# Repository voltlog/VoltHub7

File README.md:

# VoltHub7
This respository will hold the HW design files for the VoltHub7 project.
More details on youtube in Voltlog #475.

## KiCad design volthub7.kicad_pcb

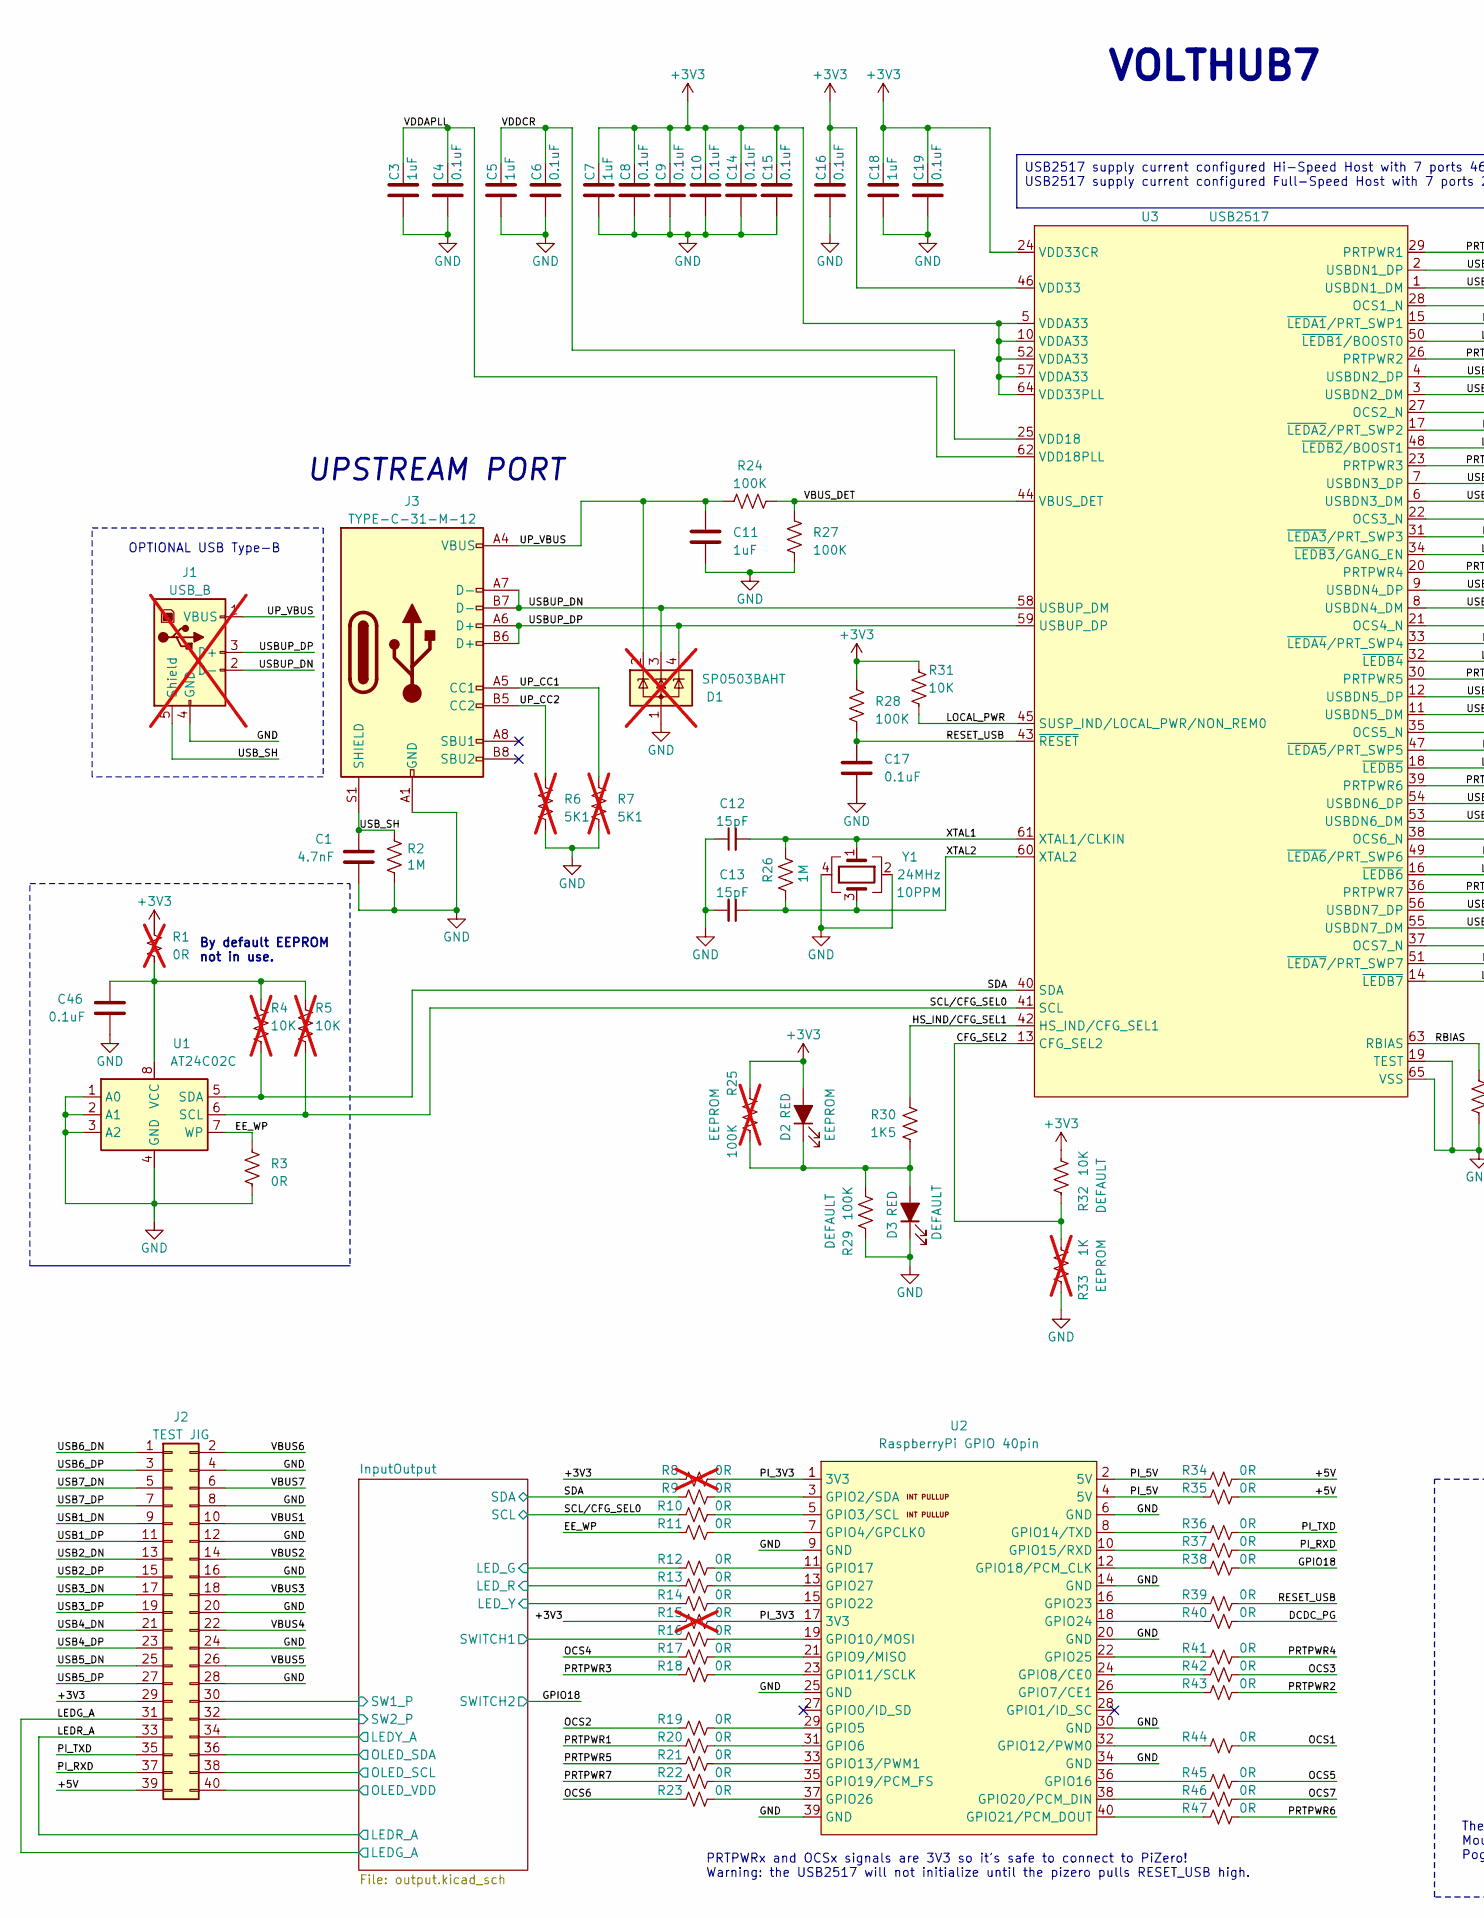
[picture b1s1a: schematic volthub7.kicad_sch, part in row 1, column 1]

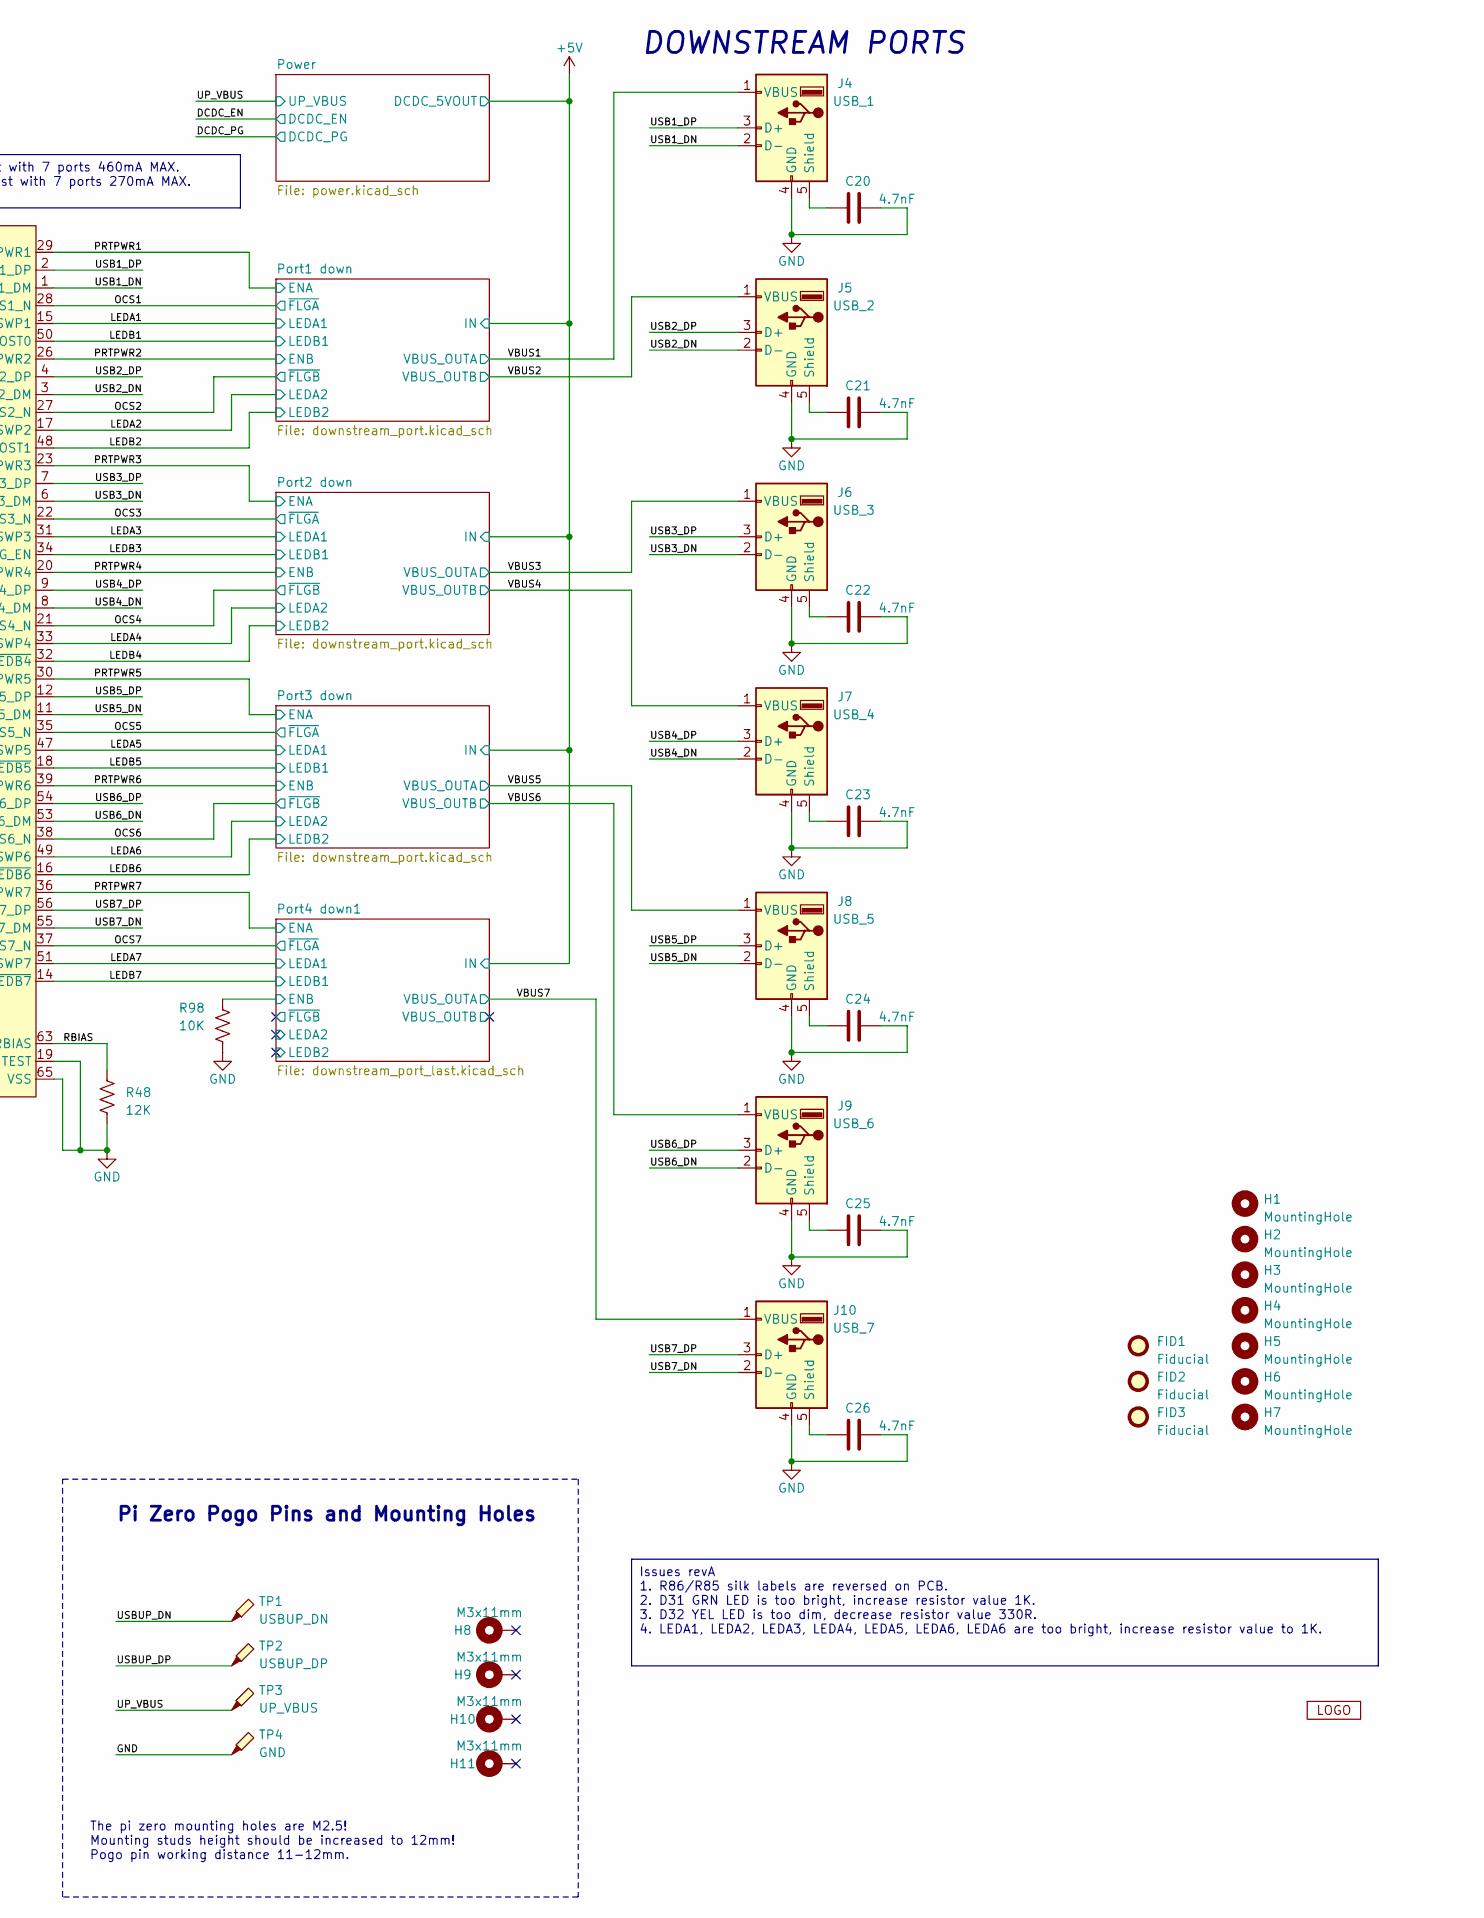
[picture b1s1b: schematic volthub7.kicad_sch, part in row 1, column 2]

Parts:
C1: 4.7nF; C_1206_3216Metric; LCSC C107198
C3, C5, C7, C11, C18: 1uF; C_0603_1608Metric
C4, C6, C8, C9, C10, C14, C15, C16, C17, C19, C46: 0.1uF; C_0603_1608Metric; LCSC C14663
C12, C13: 15pF; C_0603_1608Metric; LCSC C1644
C20, C21, C22, C23, C24, C25, C26: 4.7nF; C_1206_3216Metric; LCSC C24497
D1: SP0503BAHT; SOT-143; LCSC C2682275; not fitted
D2: EEPROM; LED_0603_1608Metric; LCSC C193902
D3: DEFAULT; LED_0603_1608Metric; LCSC C193902
FID1, FID2, FID3: Fiducial; Fiducial_0.5mm_Mask1mm
H1, H2, H3, H4, H5, H6, H7: MountingHole; MountingHole_3.2mm_M3
H8, H9, H10, H11: M3x11mm; SMTSO30100CTJ; LCSC C2916372
J1: USB_B; USB_B_Lumberg_2411_02_Horizontal; LCSC C530600; not fitted
J2: TEST JIG; JST_PHD_B32B-PHDSS_2x20_P2.00mm_Vertical; LCSC C2845630
J3: TYPE-C-31-M-12; USB_C_Receptacle_HRO_TYPE-C-31-M-12; LCSC C165948
J4: USB_1; USB_A_HRO_U-A-24DD-W-5; LCSC C530625
J5: USB_2; USB_A_HRO_U-A-24DD-W-5; LCSC C530625
J6: USB_3; USB_A_HRO_U-A-24DD-W-5; LCSC C530625
J7: USB_4; USB_A_HRO_U-A-24DD-W-5; LCSC C530625
J8: USB_5; USB_A_HRO_U-A-24DD-W-5; LCSC C530625
J9: USB_6; USB_A_HRO_U-A-24DD-W-5; LCSC C530625
J10: USB_7; USB_A_HRO_U-A-24DD-W-5; LCSC C530625
R1, R8, R15: 0R; R_0603_1608Metric; LCSC C21189; not fitted
R2: 1M; R_1206_3216Metric
R3, R9, R10, R11, R12, R13, R14, R16, R17, R18, R19, R20, R21, R22, R23, R34, R35, R36, R37, R38, R39, R40, R41, R42, R43, R44, R45, R46, R47: 0R; R_0603_1608Metric; LCSC C21189
R4, R5: 10K; R_0603_1608Metric; LCSC C25804; not fitted
R6, R7: 5K1; R_0603_1608Metric; not fitted
R24, R27, R28, R29: 100K; R_0603_1608Metric; LCSC C25803
R25: 100K; R_0603_1608Metric; LCSC C25803; not fitted
R26: 1M; R_0603_1608Metric; LCSC C22935
R30: 1K5; R_0603_1608Metric; LCSC C21190
R31, R32, R98: 10K; R_0603_1608Metric; LCSC C25804
R33: 1K; R_0603_1608Metric; LCSC C21190; not fitted
R48: 12K; R_0603_1608Metric; LCSC C22790
TP1: USBUP_DN; Pogo_pin_YZ87615160P-01; LCSC C5157295
TP2: USBUP_DP; Pogo_pin_YZ87615160P-01; LCSC C5157295
TP3: UP_VBUS; Pogo_pin_YZ87615160P-01; LCSC C5157295
TP4: GND; Pogo_pin_YZ87615160P-01; LCSC C5157295
U1: AT24C02C; SOIC-8_3.9x4.9mm_P1.27mm; LCSC C6203
U2: RaspberryPi GPIO 40pin; RaspberryPi_Zero2W_40Pin
U3: USB2517; QFN-64-1EP_9x9mm_P0.5mm_EP4.7x4.7mm; LCSC C1521556
V1: VOLTLOG_LOGO; voltlog_mask_5mm
Y1: 24MHz; Crystal_SMD_SeikoEpson_TSX3225-4Pin_3.2x2.5mm; Tolerance 10PPM; LCSC C89577

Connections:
+3V3: C7.1, C8.1, C9.1, C10.1, C14.1, C15.1, C16.1, C18.1, C19.1, D2.2 (A), J2.29, R1.2, R8.1, R15.1, R25.1, R28.2, R31.2, R32.2, U3.5 (VDDA33), U3.10 (VDDA33), U3.24 (VDD33CR), U3.46 (VDD33), U3.52 (VDDA33), U3.57 (VDDA33), U3.64 (VDD33PLL); also elsewhere on the board
+5V: J2.39, R34.2, R35.2; also elsewhere on the board
/CFG_SEL2: R32.1, R33.2, U3.13 (CFG_SEL2)
/DCDC_PG: R40.2; also elsewhere on the board
/EE_WP: R3.2, R11.1, U1.7 (WP)
/GPIO18: R38.2; also elsewhere on the board
/HS_IND/CFG_SEL1: R30.2, U3.42 (HS_IND/CFG_SEL1)
/LEDA1: U3.15 (~LEDA1/PRT_SWP1); also elsewhere on the board
/LEDA2: U3.17 (~LEDA2/PRT_SWP2); also elsewhere on the board
/LEDA3: U3.31 (~LEDA3/PRT_SWP3); also elsewhere on the board
/LEDA4: U3.33 (~LEDA4/PRT_SWP4); also elsewhere on the board
/LEDA5: U3.47 (~LEDA5/PRT_SWP5); also elsewhere on the board
/LEDA6: U3.49 (~LEDA6/PRT_SWP6); also elsewhere on the board
/LEDA7: U3.51 (~LEDA7/PRT_SWP7); also elsewhere on the board
/LEDB1: U3.50 (~LEDB1/BOOST0); also elsewhere on the board
/LEDB2: U3.48 (~LEDB2/BOOST1); also elsewhere on the board
/LEDB3: U3.34 (~LEDB3/GANG_EN); also elsewhere on the board
/LEDB4: U3.32 (~LEDB4); also elsewhere on the board
/LEDB5: U3.18 (~LEDB5); also elsewhere on the board
/LEDB6: U3.16 (~LEDB6); also elsewhere on the board
/LEDB7: U3.14 (~LEDB7); also elsewhere on the board
/LEDG_A: J2.31; also elsewhere on the board
/LEDR_A: J2.33; also elsewhere on the board
/LOCAL_PWR: R31.1, U3.45 (SUSP_IND/LOCAL_PWR/NON_REM0)
/OCS1: R44.2, U3.28 (OCS1_N); also elsewhere on the board
/OCS2: R19.1, U3.27 (OCS2_N); also elsewhere on the board
/OCS3: R42.2, U3.22 (OCS3_N); also elsewhere on the board
/OCS4: R17.1, U3.21 (OCS4_N); also elsewhere on the board
/OCS5: R45.2, U3.35 (OCS5_N); also elsewhere on the board
/OCS6: R23.1, U3.38 (OCS6_N); also elsewhere on the board
/OCS7: R46.2, U3.37 (OCS7_N); also elsewhere on the board
/Output/LEDY_A: J2.34; also elsewhere on the board
/Output/LED_G: R12.1; also elsewhere on the board
/Output/LED_R: R13.1; also elsewhere on the board
/Output/LED_Y: R14.1; also elsewhere on the board
/Output/OLED_SCL: J2.38; also elsewhere on the board
/Output/OLED_SDA: J2.36; also elsewhere on the board
/Output/OLED_VDD: J2.40; also elsewhere on the board
/Output/SW1_P: J2.30; also elsewhere on the board
/Output/SW2_P: J2.32; also elsewhere on the board
/Output/SWITCH1: R16.1; also elsewhere on the board
/PI_3V3: R8.2, R15.2, U2.1 (3V3), U2.17 (3V3)
/PI_5V: R34.1, R35.1, U2.2 (5V), U2.4 (5V)
/PI_RXD: J2.37, R37.2
/PI_TXD: J2.35, R36.2
/PRTPWR1: R20.1, U3.29 (PRTPWR1); also elsewhere on the board
/PRTPWR2: R43.2, U3.26 (PRTPWR2); also elsewhere on the board
/PRTPWR3: R18.1, U3.23 (PRTPWR3); also elsewhere on the board
/PRTPWR4: R41.2, U3.20 (PRTPWR4); also elsewhere on the board
/PRTPWR5: R21.1, U3.30 (PRTPWR5); also elsewhere on the board
/PRTPWR6: R47.2, U3.39 (PRTPWR6); also elsewhere on the board
/PRTPWR7: R22.1, U3.36 (PRTPWR7); also elsewhere on the board
/Port4 down1/ENB: R98.2; also elsewhere on the board
/RBIAS: R48.2, U3.63 (RBIAS)
/RESET_USB: C17.1, R28.1, R39.2, U3.43 (~RESET)
/SCL/CFG_SEL0: R5.1, R10.1, U1.6 (SCL), U3.41 (SCL); also elsewhere on the board
/SDA: R4.1, R9.1, U1.5 (SDA), U3.40 (SDA); also elsewhere on the board
/UP_CC1: J3.A5 (CC1), R7.2
/UP_CC2: J3.B5 (CC2), R6.2
/UP_VBUS: C11.1, D1.2 (K), J1.1 (VBUS), J3.A4 (VBUS), J3.A9 (VBUS), J3.B4 (VBUS), J3.B9 (VBUS), R24.1, TP3.1; also elsewhere on the board
/USB1_DN: J2.9, J4.2 (D-), U3.1 (USBDN1_DM)
/USB1_DP: J2.11, J4.3 (D+), U3.2 (USBDN1_DP)
/USB2_DN: J2.13, J5.2 (D-), U3.3 (USBDN2_DM)
/USB2_DP: J2.15, J5.3 (D+), U3.4 (USBDN2_DP)
/USB3_DN: J2.17, J6.2 (D-), U3.6 (USBDN3_DM)
/USB3_DP: J2.19, J6.3 (D+), U3.7 (USBDN3_DP)
/USB4_DN: J2.21, J7.2 (D-), U3.8 (USBDN4_DM)
/USB4_DP: J2.23, J7.3 (D+), U3.9 (USBDN4_DP)
/USB5_DN: J2.25, J8.2 (D-), U3.11 (USBDN5_DM)
/USB5_DP: J2.27, J8.3 (D+), U3.12 (USBDN5_DP)
/USB6_DN: J2.1, J9.2 (D-), U3.53 (USBDN6_DM)
/USB6_DP: J2.3, J9.3 (D+), U3.54 (USBDN6_DP)
/USB7_DN: J2.5, J10.2 (D-), U3.55 (USBDN7_DM)
/USB7_DP: J2.7, J10.3 (D+), U3.56 (USBDN7_DP)
/USBUP_DN: D1.3 (K), J1.2 (D-), J3.A7 (D-), J3.B7 (D-), TP1.1, U3.58 (USBUP_DM)
/USBUP_DP: D1.4 (K), J1.3 (D+), J3.A6 (D+), J3.B6 (D+), TP2.1, U3.59 (USBUP_DP)
/VBUS1: J2.10, J4.1 (VBUS); also elsewhere on the board
/VBUS2: J2.14, J5.1 (VBUS); also elsewhere on the board
/VBUS3: J2.18, J6.1 (VBUS); also elsewhere on the board
/VBUS4: J2.22, J7.1 (VBUS); also elsewhere on the board
/VBUS5: J2.26, J8.1 (VBUS); also elsewhere on the board
/VBUS6: J2.2, J9.1 (VBUS); also elsewhere on the board
/VBUS7: J2.6, J10.1 (VBUS); also elsewhere on the board
/VBUS_DET: R24.2, R27.2, U3.44 (VBUS_DET)
/VDDAPLL: C3.1, C4.1, U3.62 (VDD18PLL)
/VDDCR: C5.1, C6.1, U3.25 (VDD18)
/XTAL1: C12.2, R26.2, U3.61 (XTAL1/CLKIN), Y1.1
/XTAL2: C13.1, R26.1, U3.60 (XTAL2), Y1.3
GND: C1.2, C3.2, C4.2, C5.2, C6.2, C7.2, C8.2, C9.2, C10.2, C11.2, C12.1, C13.2, C14.2, C15.2, C16.2, C17.2, C18.2, C19.2, C20.2, C21.2, C22.2, C23.2, C24.2, C25.2, C26.2, D1.1 (A), D3.1 (K), J1.4 (GND), J2.4, J2.8, J2.12, J2.16, J2.20, J2.24, J2.28, J3.A1 (GND), J3.A12 (GND), J3.B1 (GND), J3.B12 (GND), J4.4 (GND), J5.4 (GND), J6.4 (GND), J7.4 (GND), J8.4 (GND), J9.4 (GND), J10.4 (GND), R2.2, R3.1, R6.1, R7.1, R27.1, R29.2, R33.1, R48.1, R98.1, TP4.1, U1.1 (A0), U1.2 (A1), U1.3 (A2), U1.4 (GND), U2.6 (GND), U2.9 (GND), U2.14 (GND), U2.20 (GND), U2.25 (GND), U2.30 (GND), U2.34 (GND), U2.39 (GND), U3.19 (TEST), U3.65 (VSS), Y1.2, Y1.4; also elsewhere on the board
unnamed: D2.1 (K), D3.2 (A), R25.2, R29.1, R30.1
unnamed: C20.1, J4.5 (Shield)
unnamed: C21.1, J5.5 (Shield)
unnamed: C22.1, J6.5 (Shield)
unnamed: C23.1, J7.5 (Shield)
unnamed: C24.1, J8.5 (Shield)
unnamed: C25.1, J9.5 (Shield)
unnamed: C26.1, J10.5 (Shield)
unnamed: R9.2, U2.3 (GPIO2/SDA)
unnamed: R10.2, U2.5 (GPIO3/SCL)
unnamed: R11.2, U2.7 (GPIO4/GPCLK0)
unnamed: R19.2, U2.29 (GPIO5)
unnamed: R20.2, U2.31 (GPIO6)
unnamed: R43.1, U2.26 (GPIO7/CE1)
unnamed: R42.1, U2.24 (GPIO8/CE0)
unnamed: R17.2, U2.21 (GPIO9/MISO)
unnamed: R16.2, U2.19 (GPIO10/MOSI)
unnamed: R18.2, U2.23 (GPIO11/SCLK)
unnamed: R44.1, U2.32 (GPIO12/PWM0)
unnamed: R21.2, U2.33 (GPIO13/PWM1)
unnamed: R36.1, U2.8 (GPIO14/TXD)
unnamed: R37.1, U2.10 (GPIO15/RXD)
unnamed: R45.1, U2.36 (GPIO16)
unnamed: R12.2, U2.11 (GPIO17)
unnamed: R38.1, U2.12 (GPIO18/PCM_CLK)
unnamed: R22.2, U2.35 (GPIO19/PCM_FS)
unnamed: R46.1, U2.38 (GPIO20/PCM_DIN)
unnamed: R47.1, U2.40 (GPIO21/PCM_DOUT)
unnamed: R14.2, U2.15 (GPIO22)
unnamed: R39.1, U2.16 (GPIO23)
unnamed: R40.1, U2.18 (GPIO24)
unnamed: R41.1, U2.22 (GPIO25)
unnamed: R23.2, U2.37 (GPIO26)
unnamed: R13.2, U2.13 (GPIO27)

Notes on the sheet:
USB2517 supply current configured Hi-Speed Host with 7 ports 460mA MAX. USB2517 supply current configured Full-Speed Host with 7 ports 270mA MAX.
Issues revA 1. R86/R85 silk labels are reversed on PCB. 2. D31 GRN LED is too bright, increase resistor value 1K. 3. D32 YEL LED is too dim, decrease resistor value 330R. 4. LEDA1, LEDA2, LEDA3, LEDA4, LEDA5, LEDA6, LEDA6 are too bright, increase resistor value to 1K.
The pi zero mounting holes are M2.5! Mounting studs height should be increased to 12mm! Pogo pin working distance 11-12mm.
PRTPWRx and OCSx signals are 3V3 so it's safe to connect to PiZero! Warning: the USB2517 will not initialize until the pizero pulls RESET_USB high.
OPTIONAL USB Type-B
UPSTREAM PORT
VOLTHUB7
By default EEPROM not in use.
Pi Zero Pogo Pins and Mounting Holes
DOWNSTREAM PORTS

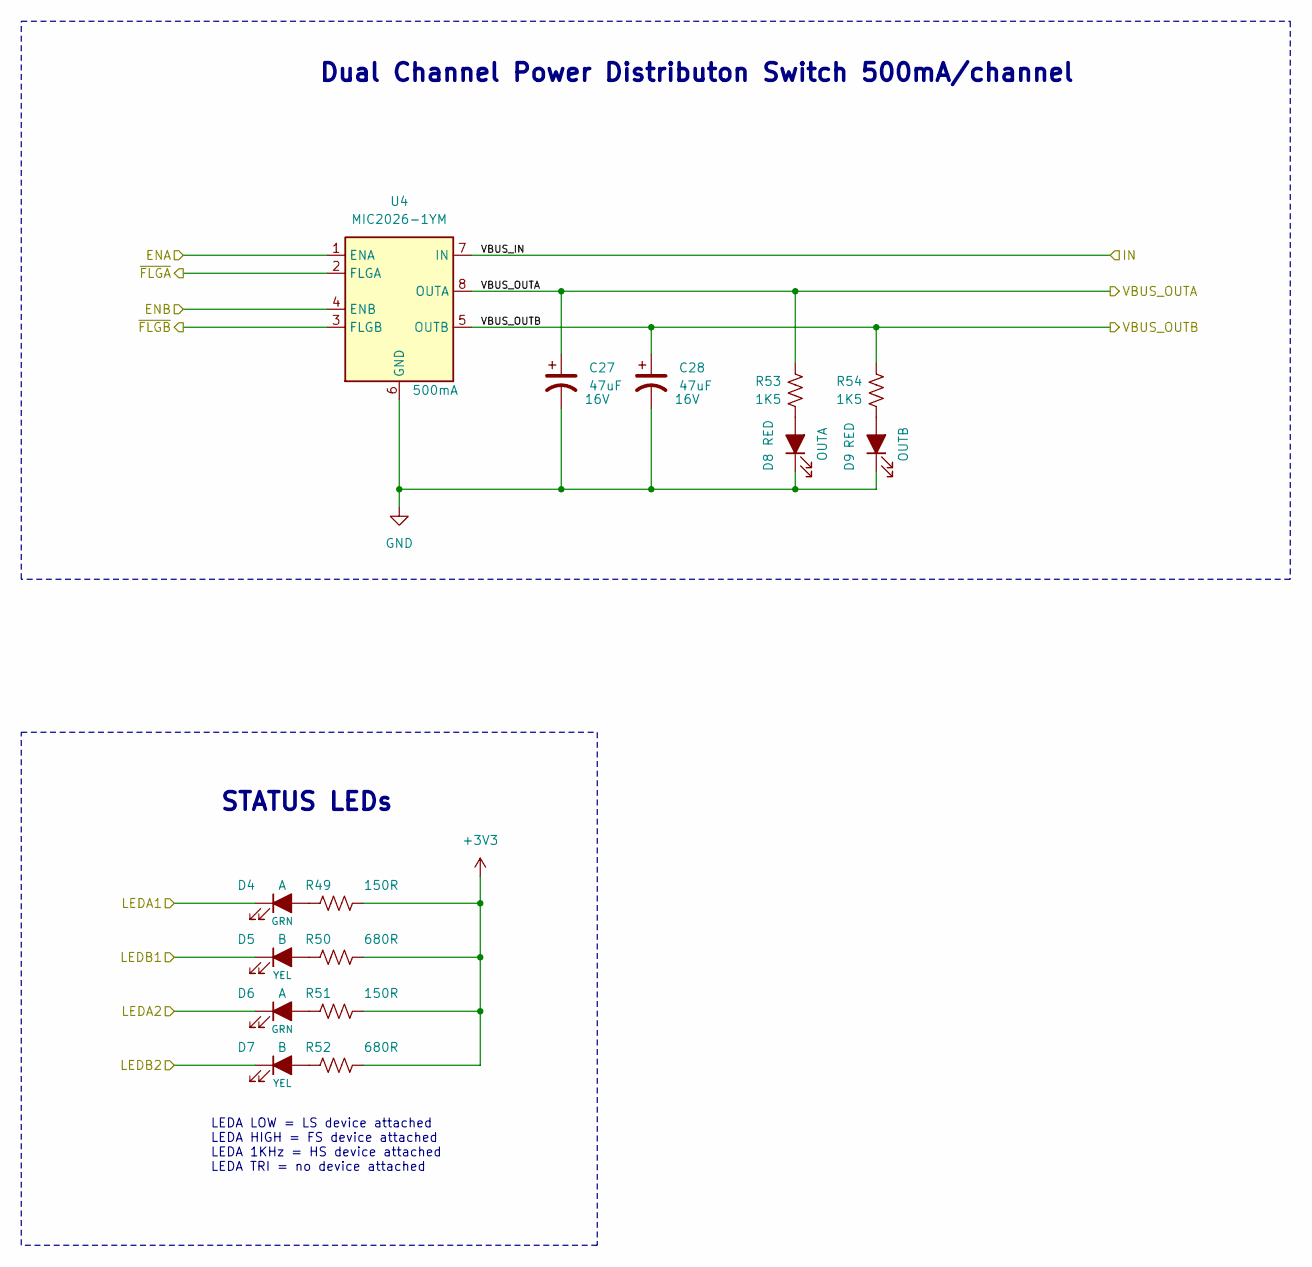
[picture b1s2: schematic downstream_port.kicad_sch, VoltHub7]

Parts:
C27, C28: 47uF; CP_Elec_6.3x5.3; Voltage 16V; LCSC C249535
D4, D6: A; LED_0603_1608Metric; LCSC C84267
D5, D7: B; LED_0603_1608Metric; LCSC C84268
D8: OUTA; LED_0603_1608Metric; LCSC C193902
D9: OUTB; LED_0603_1608Metric; LCSC C193902
R49, R51: 150R; R_0603_1608Metric; LCSC C22808
R50, R52: 680R; R_0603_1608Metric; LCSC C23228
R53, R54: 1K5; R_0603_1608Metric
U4: MIC2026-1YM; SO-8_3.9x4.9mm_P1.27mm; LCSC C144190

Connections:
+3V3: R49.2, R50.2, R51.2, R52.2; also elsewhere on the board
+5V: U4.7 (IN); also elsewhere on the board
/LEDA1: D4.1 (K); also elsewhere on the board
/LEDA2: D6.1 (K); also elsewhere on the board
/LEDB1: D5.1 (K); also elsewhere on the board
/LEDB2: D7.1 (K); also elsewhere on the board
/OCS1: U4.2 (FLGA); also elsewhere on the board
/OCS2: U4.3 (FLGB); also elsewhere on the board
/PRTPWR1: U4.1 (ENA); also elsewhere on the board
/PRTPWR2: U4.4 (ENB); also elsewhere on the board
/VBUS1: C27.1, R53.2, U4.8 (OUTA); also elsewhere on the board
/VBUS2: C28.1, R54.2, U4.5 (OUTB); also elsewhere on the board
GND: C27.2, C28.2, D8.1 (K), D9.1 (K), U4.6 (GND); also elsewhere on the board
unnamed: D4.2 (A), R49.1
unnamed: D5.2 (A), R50.1
unnamed: D6.2 (A), R51.1
unnamed: D7.2 (A), R52.1
unnamed: D8.2 (A), R53.1
unnamed: D9.2 (A), R54.1

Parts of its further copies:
C38, C39, C40, C41: 47uF; CP_Elec_6.3x5.3; Voltage 16V; LCSC C249535
D12, D14, D18, D20: A; LED_0603_1608Metric; LCSC C84267
D13, D15, D19, D21: B; LED_0603_1608Metric; LCSC C84268
D16, D22: OUTA; LED_0603_1608Metric; LCSC C193902
D17, D23: OUTB; LED_0603_1608Metric; LCSC C193902
R64, R66, R70, R72: 150R; R_0603_1608Metric; LCSC C22808
R65, R67, R71, R73: 680R; R_0603_1608Metric; LCSC C23228
R68, R69, R74, R75: 1K5; R_0603_1608Metric
U7, U8: MIC2026-1YM; SO-8_3.9x4.9mm_P1.27mm; LCSC C144190

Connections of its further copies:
+3V3: R64.2, R65.2, R66.2, R67.2, R70.2, R71.2, R72.2, R73.2; also elsewhere on the board
+5V: U7.7 (IN), U8.7 (IN); also elsewhere on the board
/LEDA3: D12.1 (K); also elsewhere on the board
/LEDA4: D14.1 (K); also elsewhere on the board
/LEDA5: D18.1 (K); also elsewhere on the board
/LEDA6: D20.1 (K); also elsewhere on the board
/LEDB3: D13.1 (K); also elsewhere on the board
/LEDB4: D15.1 (K); also elsewhere on the board
/LEDB5: D19.1 (K); also elsewhere on the board
/LEDB6: D21.1 (K); also elsewhere on the board
/OCS3: U7.2 (FLGA); also elsewhere on the board
/OCS4: U7.3 (FLGB); also elsewhere on the board
/OCS5: U8.2 (FLGA); also elsewhere on the board
/OCS6: U8.3 (FLGB); also elsewhere on the board
/PRTPWR3: U7.1 (ENA); also elsewhere on the board
/PRTPWR4: U7.4 (ENB); also elsewhere on the board
/PRTPWR5: U8.1 (ENA); also elsewhere on the board
/PRTPWR6: U8.4 (ENB); also elsewhere on the board
/VBUS3: C38.1, R68.2, U7.8 (OUTA); also elsewhere on the board
/VBUS4: C39.1, R69.2, U7.5 (OUTB); also elsewhere on the board
/VBUS5: C40.1, R74.2, U8.8 (OUTA); also elsewhere on the board
/VBUS6: C41.1, R75.2, U8.5 (OUTB); also elsewhere on the board
GND: C38.2, C39.2, C40.2, C41.2, D16.1 (K), D17.1 (K), D22.1 (K), D23.1 (K), U7.6 (GND), U8.6 (GND); also elsewhere on the board
unnamed: D12.2 (A), R64.1
unnamed: D13.2 (A), R65.1
unnamed: D14.2 (A), R66.1
unnamed: D15.2 (A), R67.1
unnamed: D16.2 (A), R68.1
unnamed: D17.2 (A), R69.1
unnamed: D18.2 (A), R70.1
unnamed: D19.2 (A), R71.1
unnamed: D20.2 (A), R72.1
unnamed: D21.2 (A), R73.1
unnamed: D22.2 (A), R74.1
unnamed: D23.2 (A), R75.1

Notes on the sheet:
Dual Channel Power Distributon Switch 500mA/channel
STATUS LEDs
LEDA LOW = LS device attached LEDA HIGH = FS device attached LEDA 1KHz = HS device attached LEDA TRI = no device attached

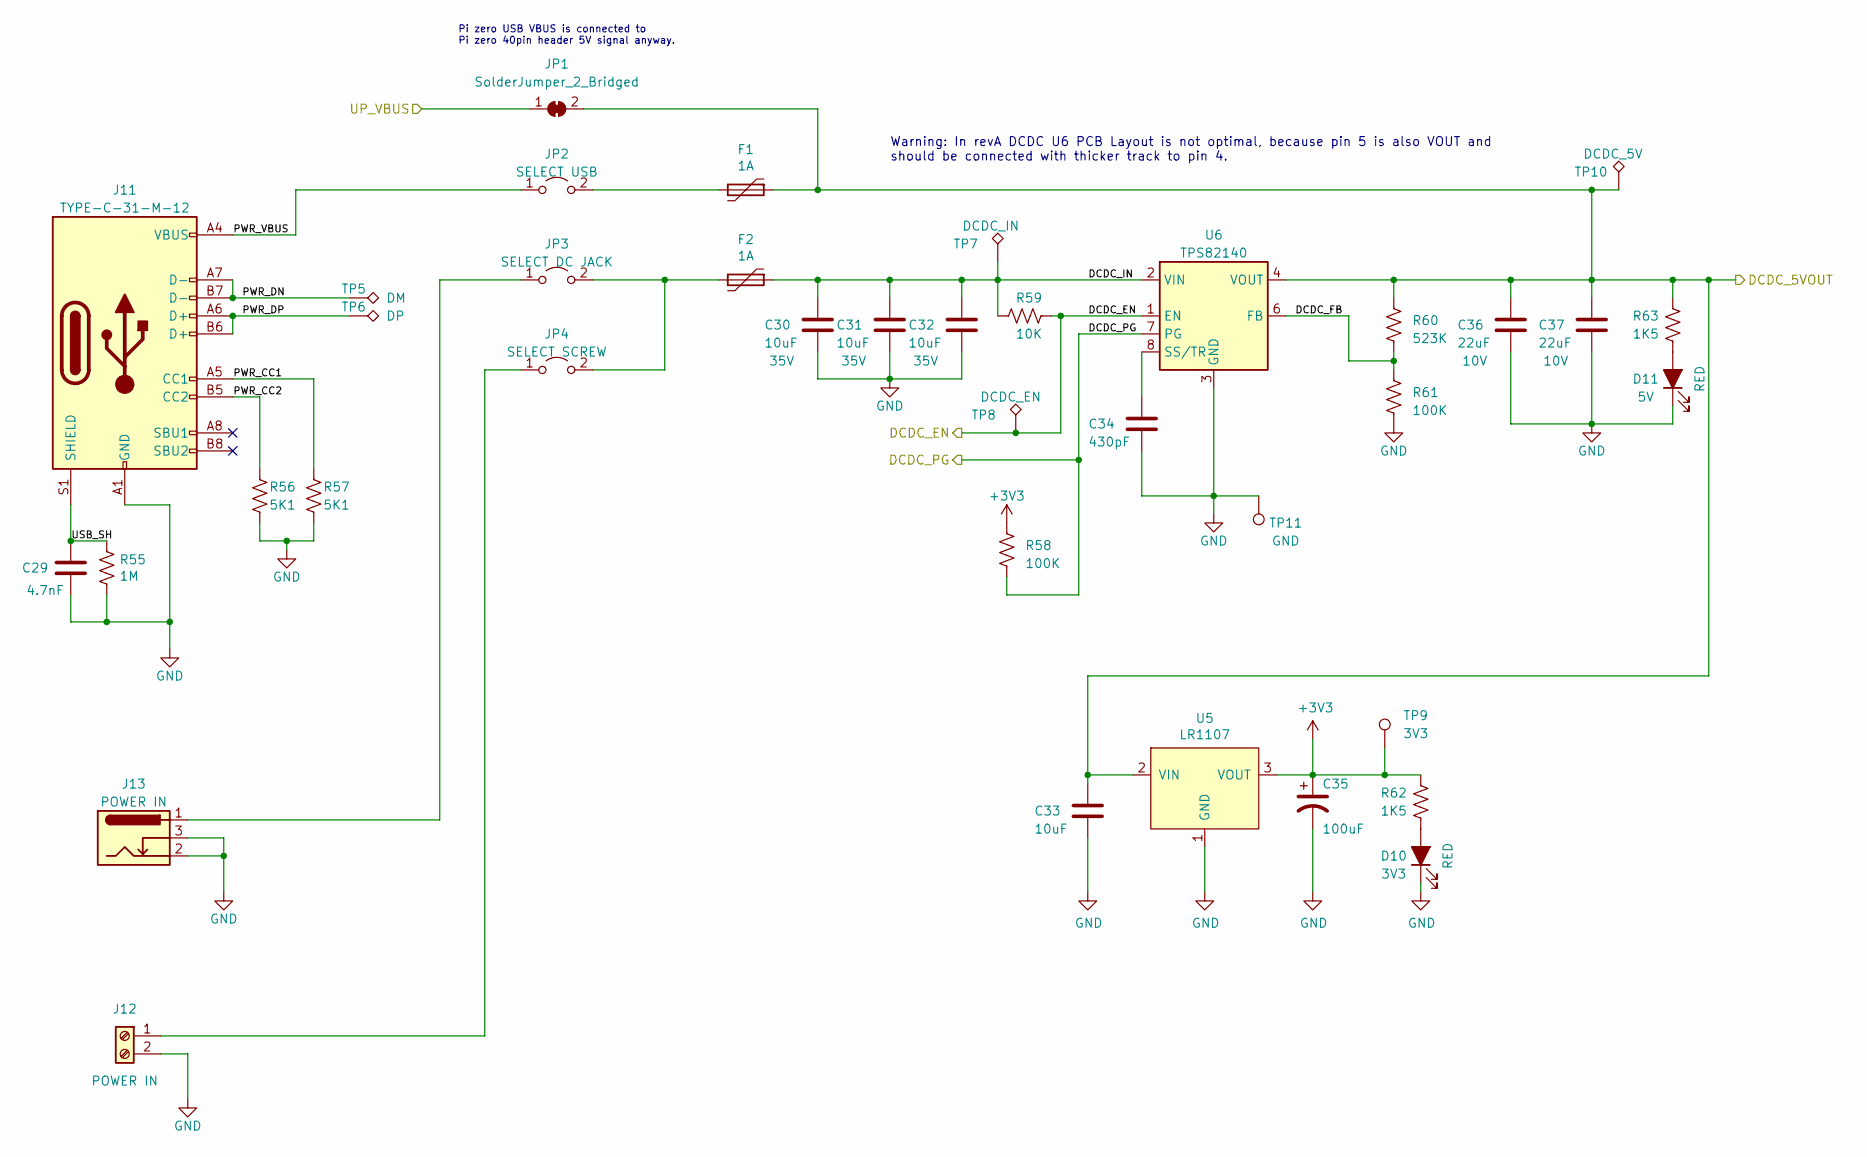
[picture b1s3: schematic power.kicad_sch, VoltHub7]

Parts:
C29: 4.7nF; C_1206_3216Metric; LCSC C107198
C30, C31, C32, C33: 10uF; C_0805_2012Metric; Voltage 35V; LCSC C162422
C34: 430pF; C_0603_1608Metric; LCSC C309472
C35: 100uF; CP_Elec_6.3x5.8; Voltage 10V; LCSC C340720
C36, C37: 22uF; C_0805_2012Metric; Voltage 10V; LCSC C29277
D10: 3V3; LED_0603_1608Metric; LCSC C193902
D11: 5V; LED_0603_1608Metric; LCSC C193902
F1, F2: 1A; Fuse_0805_2012Metric; LCSC C369152
J11: TYPE-C-31-M-12; USB_C_Receptacle_HRO_TYPE-C-31-M-12; LCSC C165948
J12: POWER IN; TerminalBlock_RND_205-00287_1x02_P5.08mm_Horizontal
J13: POWER IN; BarrelJack_CLIFF_FC681465S_SMT_Horizontal; LCSC C2987414
JP1: SolderJumper_2_Bridged; SolderJumper-2_P1.3mm_Bridged_RoundedPad1.0x1.5mm
JP2: SELECT USB; PinHeader_1x02_P2.54mm_Vertical
JP3: SELECT DC JACK; PinHeader_1x02_P2.54mm_Vertical
JP4: SELECT SCREW; PinHeader_1x02_P2.54mm_Vertical
R55: 1M; R_1206_3216Metric
R56, R57: 5K1; R_0603_1608Metric
R58, R61: 100K; R_0603_1608Metric; LCSC C25803
R59: 10K; R_0603_1608Metric; LCSC C25804
R60: 523K; R_0603_1608Metric; LCSC C5126197
R62: 1K5; R_0603_1608Metric; LCSC C21190
R63: 1K5; R_0603_1608Metric
TP5: DM; TestPoint_Pad_D1.0mm
TP6: DP; TestPoint_Pad_D1.0mm
TP7: DCDC_IN; TestPoint_Pad_D1.0mm
TP8: DCDC_EN; TestPoint_Pad_D1.0mm
TP9: 3V3; TestPoint_Pad_D1.0mm
TP10: DCDC_5V; TestPoint_Pad_D1.0mm
TP11: GND; TestPoint_Keystone_5019_Minature; LCSC C238131
U5: LR1107; SOT-89-3; LCSC C171498
U6: TPS82140; Texas_SIL0008D_MicroSiP-8-1EP_2.8x3mm_P0.65mm_EP1.1x1.9mm

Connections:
+3V3: C35.1, R58.2, R62.2, TP9.1, U5.3 (VOUT); also elsewhere on the board
+5V: C33.1, C36.1, C37.1, F1.1, JP1.2 (B), R60.2, R63.2, TP10.1, U5.2 (VIN), U6.4 (VOUT), U6.5 (VOUT); also elsewhere on the board
/DCDC_EN: R59.1, TP8.1, U6.1 (EN)
/DCDC_PG: R58.1, U6.7 (PG); also elsewhere on the board
/Power/DCDC_FB: R60.1, R61.2, U6.6 (FB)
/Power/DCDC_IN: C30.1, C31.1, C32.1, F2.1, R59.2, TP7.1, U6.2 (VIN)
/Power/PWR_CC1: J11.A5 (CC1), R57.2
/Power/PWR_CC2: J11.B5 (CC2), R56.2
/Power/PWR_DN: J11.A7 (D-), J11.B7 (D-), TP5.1
/Power/PWR_DP: J11.A6 (D+), J11.B6 (D+), TP6.1
/Power/PWR_VBUS: J11.A4 (VBUS), J11.A9 (VBUS), J11.B4 (VBUS), J11.B9 (VBUS), JP2.1 (A)
/Power/USB_SH: C29.1, J11.S1 (SHIELD), R55.1
/UP_VBUS: JP1.1 (A); also elsewhere on the board
GND: C29.2, C30.2, C31.2, C32.2, C33.2, C34.2, C35.2, C36.2, C37.2, D10.1 (K), D11.1 (K), J11.A1 (GND), J11.A12 (GND), J11.B1 (GND), J11.B12 (GND), J12.2, J13.2, J13.3, R55.2, R56.1, R57.1, R61.1, TP11.1, U5.1 (GND), U6.3 (GND), U6.9 (GND); also elsewhere on the board
unnamed: D10.2 (A), R62.1
unnamed: D11.2 (A), R63.1
unnamed: J12.1, JP4.1 (A)
unnamed: F1.2, JP2.2 (B)
unnamed: J13.1, JP3.1 (A)
unnamed: F2.2, JP3.2 (B), JP4.2 (B)
unnamed: C34.1, U6.8 (SS/TR)

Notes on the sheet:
Pi zero USB VBUS is connected to Pi zero 40pin header 5V signal anyway.
Warning: In revA DCDC U6 PCB Layout is not optimal, because pin 5 is also VOUT and should be connected with thicker track to pin 4.

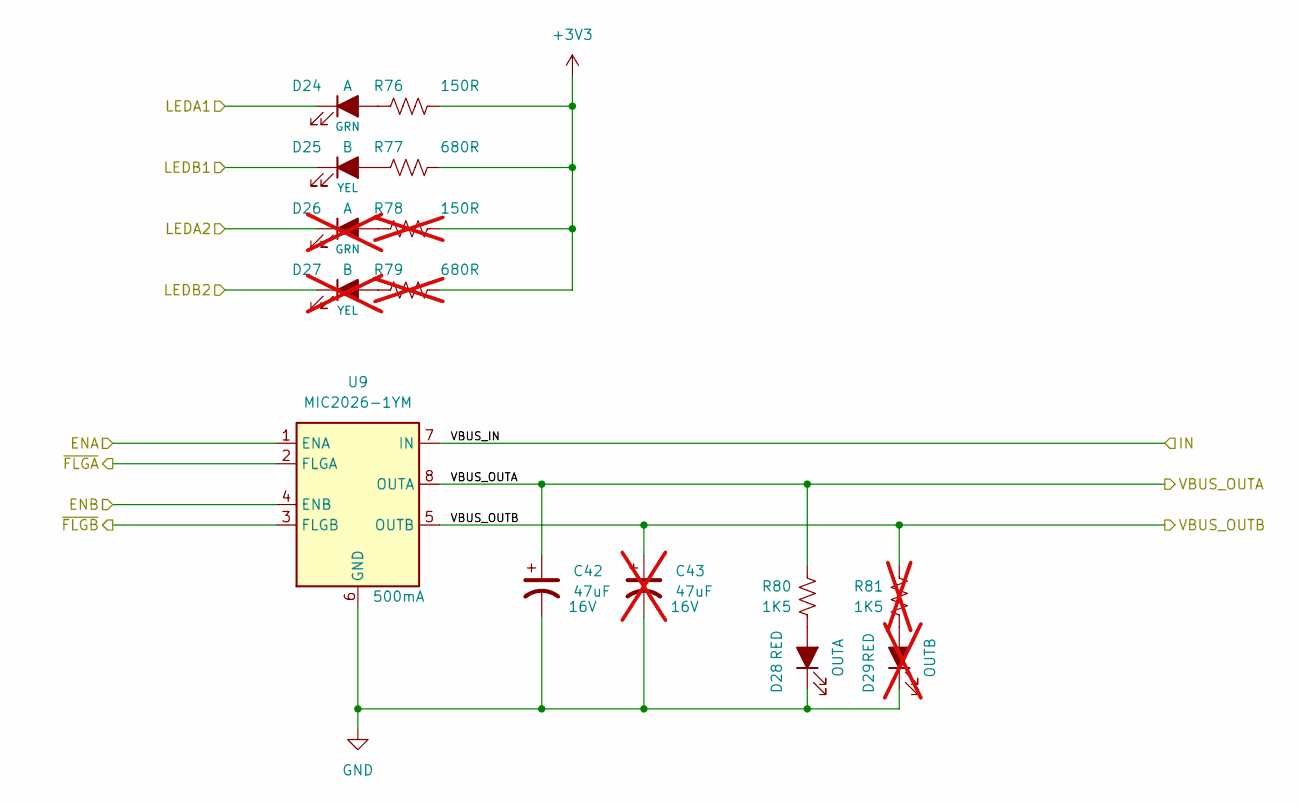
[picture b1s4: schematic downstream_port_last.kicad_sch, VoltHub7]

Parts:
C42: 47uF; CP_Elec_6.3x5.3; Voltage 16V; LCSC C249535
C43: 47uF; CP_Elec_6.3x5.3; Voltage 16V; LCSC C249535; not fitted
D24: A; LED_0603_1608Metric; LCSC C84267
D25: B; LED_0603_1608Metric; LCSC C84268
D26: A; LED_0603_1608Metric; LCSC C84267; not fitted
D27: B; LED_0603_1608Metric; LCSC C84268; not fitted
D28: OUTA; LED_0603_1608Metric; LCSC C193902
D29: OUTB; LED_0603_1608Metric; LCSC C193902; not fitted
R76: 150R; R_0603_1608Metric; LCSC C22808
R77: 680R; R_0603_1608Metric; LCSC C23228
R78: 150R; R_0603_1608Metric; LCSC C22808; not fitted
R79: 680R; R_0603_1608Metric; LCSC C23228; not fitted
R80: 1K5; R_0603_1608Metric
R81: 1K5; R_0603_1608Metric; not fitted
U9: MIC2026-1YM; SO-8_3.9x4.9mm_P1.27mm; LCSC C144190

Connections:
+3V3: R76.2, R77.2, R78.2, R79.2; also elsewhere on the board
+5V: U9.7 (IN); also elsewhere on the board
/LEDA7: D24.1 (K); also elsewhere on the board
/LEDB7: D25.1 (K); also elsewhere on the board
/OCS7: U9.2 (FLGA); also elsewhere on the board
/PRTPWR7: U9.1 (ENA); also elsewhere on the board
/Port4 down1/ENB: U9.4 (ENB); also elsewhere on the board
/Port4 down1/VBUS_OUTB: C43.1, R81.2, U9.5 (OUTB)
/Port4 down1/~FLGB: U9.3 (FLGB)
/VBUS7: C42.1, R80.2, U9.8 (OUTA); also elsewhere on the board
GND: C42.2, C43.2, D28.1 (K), D29.1 (K), U9.6 (GND); also elsewhere on the board
unnamed: D24.2 (A), R76.1
unnamed: D25.2 (A), R77.1
unnamed: D26.2 (A), R78.1
unnamed: D27.2 (A), R79.1
unnamed: D28.2 (A), R80.1
unnamed: D29.2 (A), R81.1

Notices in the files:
downstream_port.kicad_sch:
License GPLv3
